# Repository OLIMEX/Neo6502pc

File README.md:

# Neo6502pc
World fastest 6502 computer. All in one Open Source Hardware and Software Modern Retro computer with real 6502 processor, HDMI, USB Flash drive, USB Gamepads, mouse, Keyboard support.

https://www.olimex.com/Products/Retro-Computers/Neo6502pc/open-source-hardware

## Licensee
* Hardware is released under CERN Open Hardware Licence Version 2 - Strongly Reciprocal
* Software is released under GPL V3 Licensee
* Documentation is released under CC BY-SA 4.0

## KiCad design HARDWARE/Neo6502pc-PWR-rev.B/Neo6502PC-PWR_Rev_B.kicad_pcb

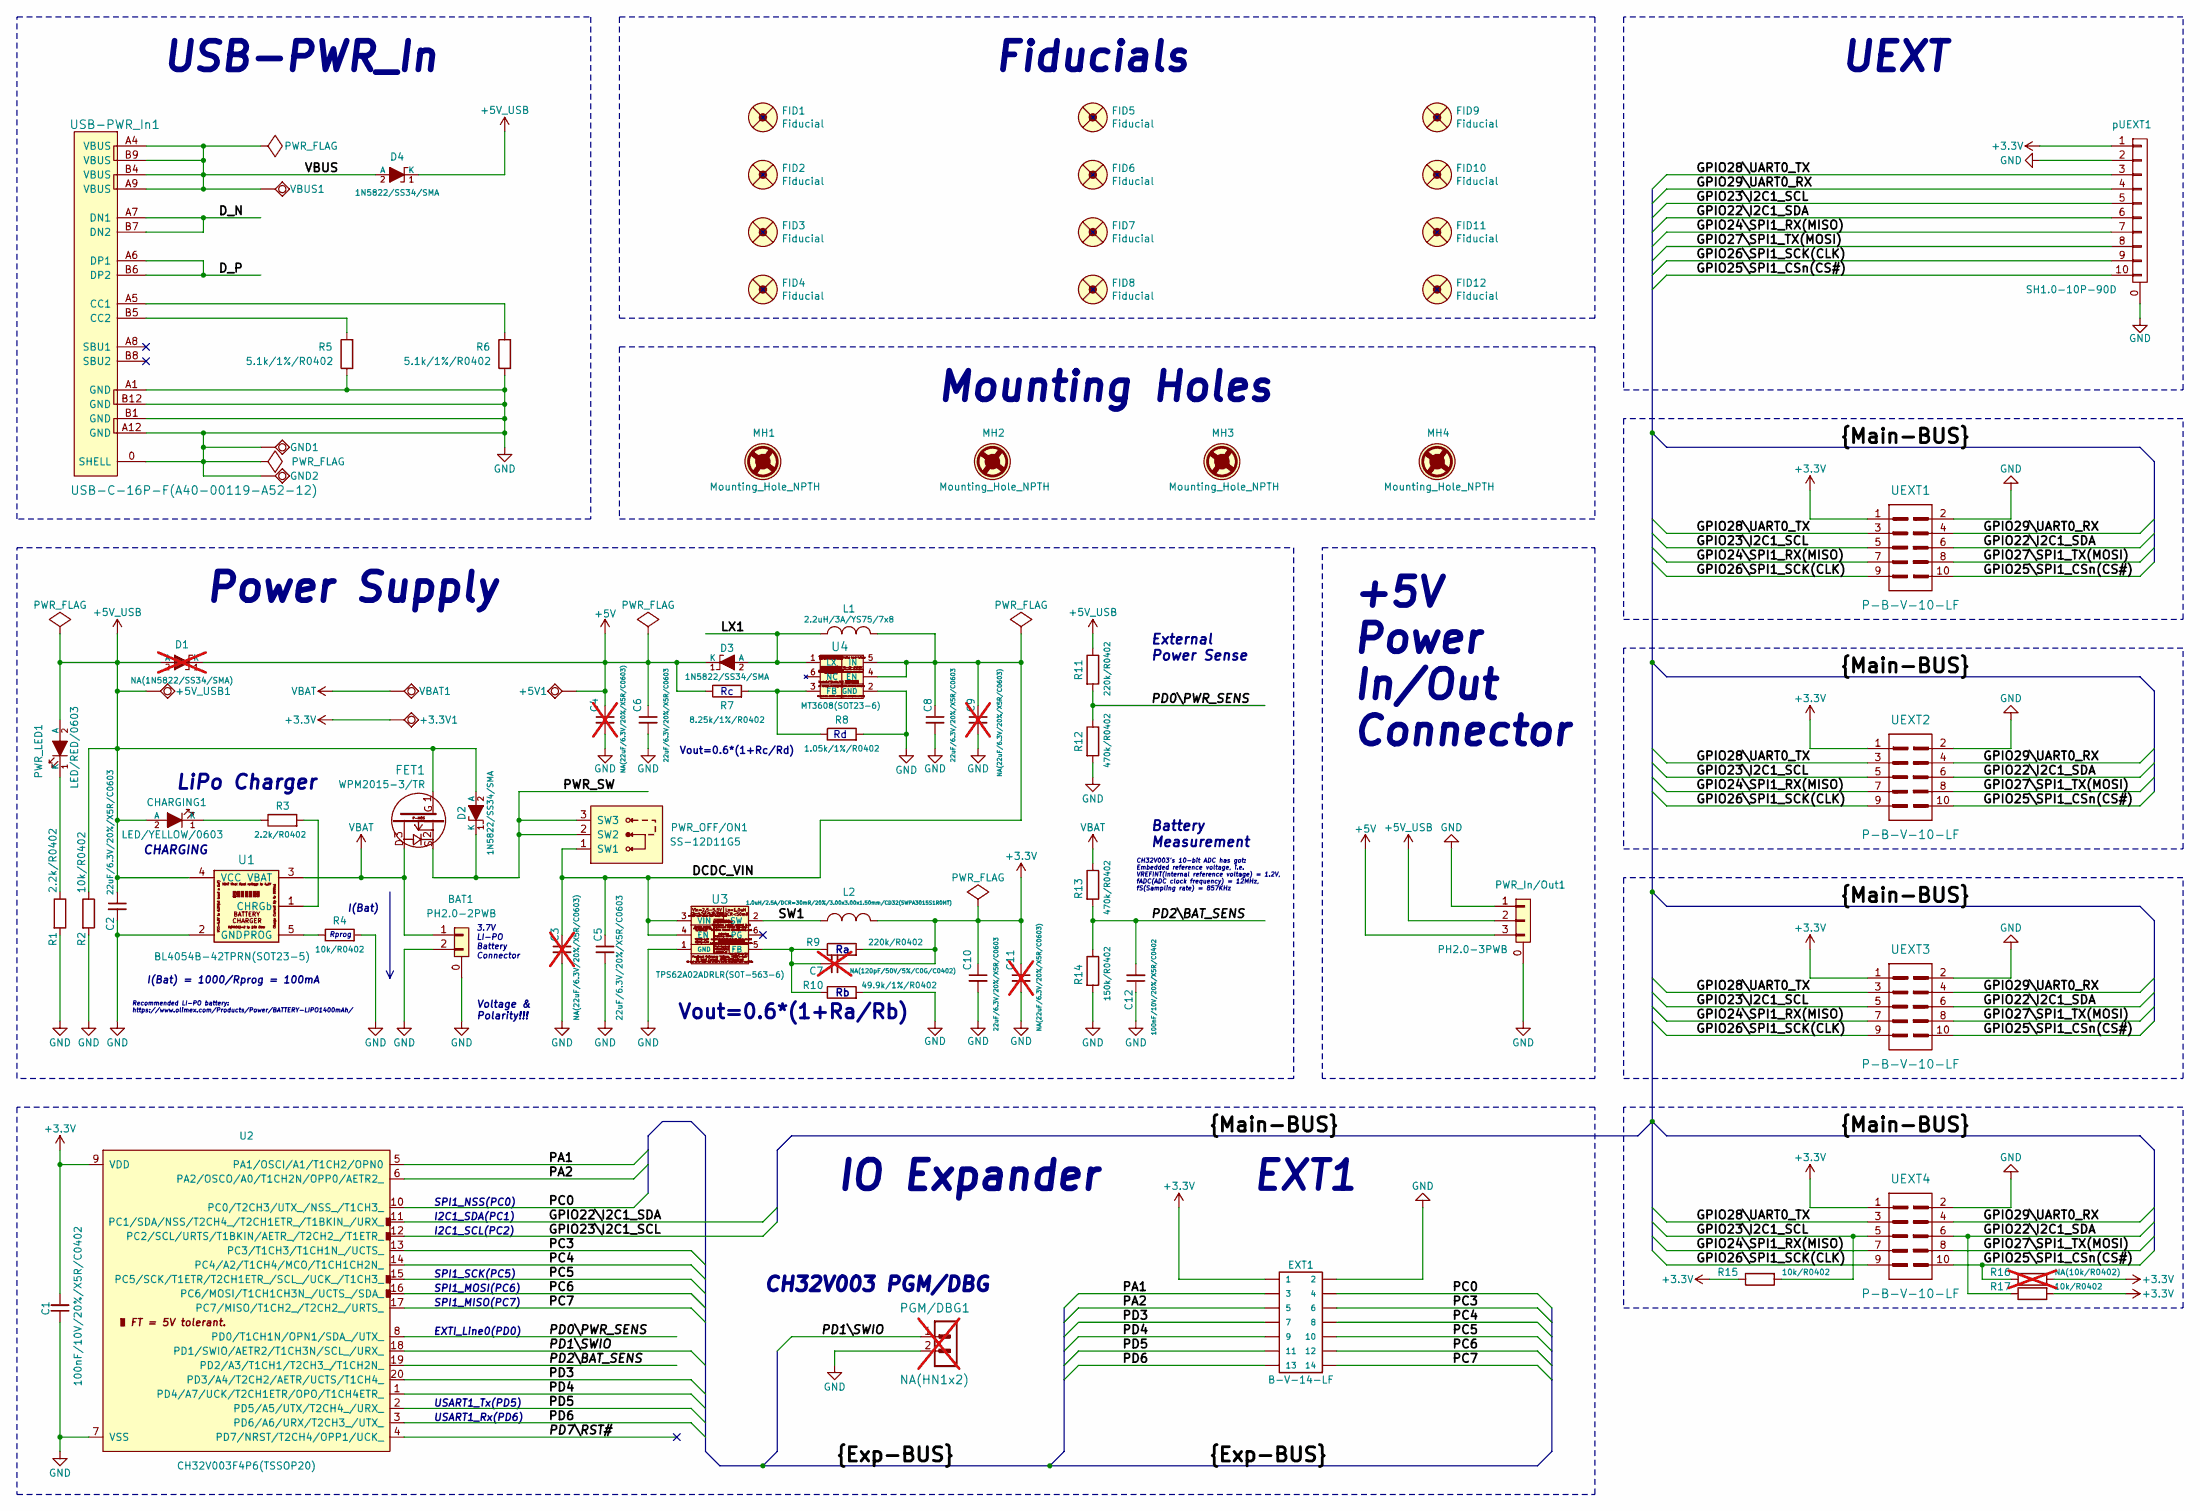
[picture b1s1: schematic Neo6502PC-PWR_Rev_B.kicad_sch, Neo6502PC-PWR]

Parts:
+3.3V1, +5V1, +5V_USB1: TESTPAD; TEST_PAD40x70_SQUARE
BAT1: PH2.0-2PWB
C1, C12: 100nF/10V/20%/X5R/C0402; C_0402_5MIL_DWS
C2, C5, C6, C8, C10: 22uF/6.3V/20%/X5R/C0603; C_0603_5MIL_DWS
C3, C4, C9, C11: NA(22uF/6.3V/20%/X5R/C0603); C_0603_5MIL_DWS; not fitted
C7: NA(120pF/50V/5%/C0G/C0402); C_0402_5MIL_DWS; not fitted
CHARGING1: LED/YELLOW/0603; LED_0603_KA
D1: NA(1N5822/SS34/SMA); SMA-KA; not fitted
D2, D3, D4: 1N5822/SS34/SMA; SMA-KA
EXT1: B-V-14-LF; GBH-254-SMT-14
FET1: WPM2015-3/TR; SOT23
FID1, FID2, FID3, FID4, FID5, FID7: Fiducial; Fiducial1x3_Paste
FID6, FID8, FID9, FID10, FID11, FID12: Fiducial; Fiducial1x3
GND1, GND2: TESTPAD; TEST_PAD40x70_SQUARE
L1: 2.2uH/3A/YS75/7x8; YS75_7X8MM
L2: 1.0uH/2.5A/DCR=30mR/20%/3.00x3.00x1.50mm/CD32(SWP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; CD32
MH1, MH2, MH3, MH4: Mounting_Hole_NPTH; Mounting_Hole_Drill-3.3mm_Clerance-7mm
PGM/DBG1: NA(HN1x2); HN1x2; not fitted
PWR_In/Out1: PH2.0-3PWB
PWR_LED1: LED/RED/0603; LED_0603_KA
PWR_OFF/ON1: SS-12D11G5
R1, R3: 2.2k/R0402; R_0402_5MIL_DWS
R2, R4, R15, R17: 10k/R0402; R_0402_5MIL_DWS
R5, R6: 5.1k/1%/R0402; R_0402_5MIL_DWS
R7: 8.25k/1%/R0402; R_0402_5MIL_DWS
R8: 1.05k/1%/R0402; R_0402_5MIL_DWS
R9, R11: 220k/R0402; R_0402_5MIL_DWS
R10: 49.9k/1%/R0402; R_0402_5MIL_DWS
R12, R13: 470k/R0402; R_0402_5MIL_DWS
R14: 150k/R0402; R_0402_5MIL_DWS
R16: NA(10k/R0402); R_0402_5MIL_DWS; not fitted
U1: BL4054B-42TPRN(SOT23-5); SOT-23-5
U2: CH32V003F4P6(TSSOP20); TSSOP20_Pitch-0.65mm_6.6x4.5x1.2mm
U3: TPS62A02ADRLR(SOT-563-6); SOT-563-6
U4: MT3608(SOT23-6); SOT23-6
UEXT1, UEXT2, UEXT3, UEXT4: P-B-V-10-LF; GBH-254-SMT-10
USB-PWR_In1: USB-C-16P-F(A40-00119-A52-12); USB2.0_TYPE-C(A40-00119-A52-12)_Paste
VBAT1: TESTPAD; TEST_PAD40x70_SQUARE
VBUS1: TESTPAD; TEST_PAD40x70_SQUARE
pUEXT1: SH1.0-10P-90D; SM10B-SRSS-TB

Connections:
+3.3V: +3.3V1.1 (Pad), C1.2, C7.2, C10.1, C11.1, EXT1.1, L2.2, R9.2, R15.1, R16.2, R17.2, U2.9 (VDD), UEXT1.1, UEXT2.1, UEXT3.1, UEXT4.1, pUEXT1.1
+5V: +5V1.1 (Pad), C4.1, C6.1, D1.1 (K), D3.1 (K), PWR_In/Out1.3 (P2), R7.1
+5V_USB: +5V_USB1.1 (Pad), C2.1, CHARGING1.2 (A), D1.2 (A), D2.2 (A), D4.1 (K), FET1.1, PWR_In/Out1.2, PWR_LED1.2 (A), R2.1, R11.1, U1.4 (VCC)
/DCDC_VIN: C3.1, C5.1, C8.1, C9.1, L1.2, PWR_OFF/ON1.1 (SW1), U3.3 (VIN), U3.4 (EN), U4.4 (EN), U4.5 (IN)
/D_N: USB-PWR_In1.A7 (DN1), USB-PWR_In1.B7 (DN2)
/D_P: USB-PWR_In1.A6 (DP1), USB-PWR_In1.B6 (DP2)
/GPIO22\I2C1_SDA: R17.1, U2.11 (PC1/SDA/NSS/T2CH4_/T2CH1ETR_/T1BKIN_/UR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), UEXT1.6, UEXT2.6, UEXT3.6, UEXT4.6, pUEXT1.6
/GPIO23\I2C1_SCL: R15.2, U2.12 (PC2/SCL/URTS/T1BKIN/AETR_/T2CH2_/T1ETR_), UEXT1.5, UEXT2.5, UEXT3.5, UEXT4.5, pUEXT1.5
/GPIO24\SPI1_RX(MISO): UEXT1.7, UEXT2.7, UEXT3.7, UEXT4.7, pUEXT1.7
/GPIO25\SPI1_CSn(CS#): R16.1, UEXT1.10, UEXT2.10, UEXT3.10, UEXT4.10, pUEXT1.10
/GPIO26\SPI1_SCK(CLK): UEXT1.9, UEXT2.9, UEXT3.9, UEXT4.9, pUEXT1.9
/GPIO27\SPI1_TX(MOSI): UEXT1.8, UEXT2.8, UEXT3.8, UEXT4.8, pUEXT1.8
/GPIO28\UART0_TX: UEXT1.3, UEXT2.3, UEXT3.3, UEXT4.3, pUEXT1.3
/GPIO29\UART0_RX: UEXT1.4, UEXT2.4, UEXT3.4, UEXT4.4, pUEXT1.4
/LX1: D3.2 (A), L1.1, U4.1 (LX)
/PA1: EXT1.3, U2.5 (PA1/OSCI/A1/T1CH2/OPN0)
/PA2: EXT1.5, U2.6 (PA2/OSCO/A0/T1CH2N/OPP0/AETR2_)
/PC0: EXT1.4, U2.10 (PC0/T2CH3/UTX_/NSS_/T1CH3_)
/PC3: EXT1.6, U2.13 (PC3/T1CH3/T1CH1N_/UCTS_)
/PC4: EXT1.8, U2.14 (PC4/A2/T1CH4/MCO/T1CH1CH2N_)
/PC5: EXT1.10, U2.15 (PC5/SCK/T1ETR/T2CH1ETR_/SCL_/UCK_/T1CH3_)
/PC6: EXT1.12, U2.16 (PC6/MOSI/T1CH1CH3N_/UCTS_/SDA_)
/PC7: EXT1.14, U2.17 (PC7/MISO/T1CH2_/T2CH2_/URTS_)
/PD0\PWR_SENS: R11.2, R12.1, U2.8 (PD0/T1CH1N/OPN1/SDA_/UTX_)
/PD1\SWIO: PGM/DBG1.1, U2.18 (PD1/SWIO/AETR2/T1CH3N/SCL_/URX_)
/PD2\BAT_SENS: C12.2, R13.2, R14.1, U2.19 (PD2/A3/T1CH1/T2CH3_/T1CH2N_)
/PD3: EXT1.7, U2.20 (PD3/A4/T2CH2/AETR/UCTS/T1CH4_)
/PD4: EXT1.9, U2.1 (PD4/A7/UCK/T2CH1ETR/OPO/T1CH4ETR_)
/PD5: EXT1.11, U2.2 (PD5/A5/UTX/T2CH4_/URX_)
/PD6: EXT1.13, U2.3 (PD6/A6/URX/T2CH3_/UTX_)
/PD7\RST#: U2.4 (PD7/NRST/T2CH4/OPP1/UCK_)
/PWR_SW: D2.1 (K), FET1.2, PWR_OFF/ON1.2 (SW2), PWR_OFF/ON1.3 (SW3)
/SW1: L2.1, U3.2 (SW)
/VBUS: D4.2 (A), USB-PWR_In1.A4 (VBUS), USB-PWR_In1.A9 (VBUS), USB-PWR_In1.B4 (VBUS), USB-PWR_In1.B9 (VBUS), VBUS1.1 (Pad)
GND: BAT1.0, BAT1.2, C1.1, C2.2, C3.2, C4.2, C5.2, C6.2, C8.2, C9.2, C10.2, C11.2, C12.1, EXT1.2, GND1.1 (Pad), GND2.1 (Pad), PGM/DBG1.2, PWR_In/Out1.0, PWR_In/Out1.1, R1.2, R2.2, R4.2, R5.1, R6.1, R8.2, R10.2, R12.2, R14.2, U1.2 (GND), U2.7 (VSS), U3.1 (GND), U4.2 (GND), UEXT1.2, UEXT2.2, UEXT3.2, UEXT4.2, USB-PWR_In1.0 (SHELL), USB-PWR_In1.A1 (GND), USB-PWR_In1.A12 (GND), USB-PWR_In1.B1 (GND), USB-PWR_In1.B12 (GND), pUEXT1.0, pUEXT1.2
unnamed: CHARGING1.1 (K), R3.1
unnamed: PWR_LED1.1 (K), R1.1
unnamed: R3.2, U1.1 (CHRGb)
unnamed: R4.1, U1.5 (PROG)
unnamed: C7.1, R9.1, R10.1, U3.5 (FB)
unnamed: R7.2, R8.1, U4.3 (FB)
unnamed: R6.2, USB-PWR_In1.A5 (CC1)
unnamed: R5.2, USB-PWR_In1.B5 (CC2)
VBAT: BAT1.1, FET1.3, R13.1, U1.3 (VBAT), VBAT1.1 (Pad)

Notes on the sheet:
I(Bat) = 1000/Rprog = 100mA
CHARGING
CH32V003 PGM/DBG
SPI1_MOSI(PC6)
Rprog
External Power Sense
I2C1_SCL(PC2)
SPI1_MISO(PC7)
Fiducials
EXT1
Recommended LI-PO battery: https://www.olimex.com/Products/Power/BATTERY-LIPO1400mAh/
LiPo Charger
Power Supply
I(Bat)
Mounting Holes
EXTI_Line0(PD0)
I2C1_SDA(PC1)
USART1_Rx(PD6)
Vout=0.6*(1+Rc/Rd)
Vout=0.6*(1+Ra/Rb)
SPI1_NSS(PC0)
USART1_Tx(PD5)
3.7V LI-PO Battery Connector
CH32V003's 10-bit ADC has got: Embedded reference voltage, i.e. VREFINT(Internal reference voltage) = 1.2V, fADC(ADC clock frequency) = 12MHz, fS(Sampling rate) = 857KHz
UEXT
IO Expander
+5V Power In/Out Connector
SPI1_SCK(PC5)
USB-PWR_In
Voltage & Polarity!!!
Battery Measurement

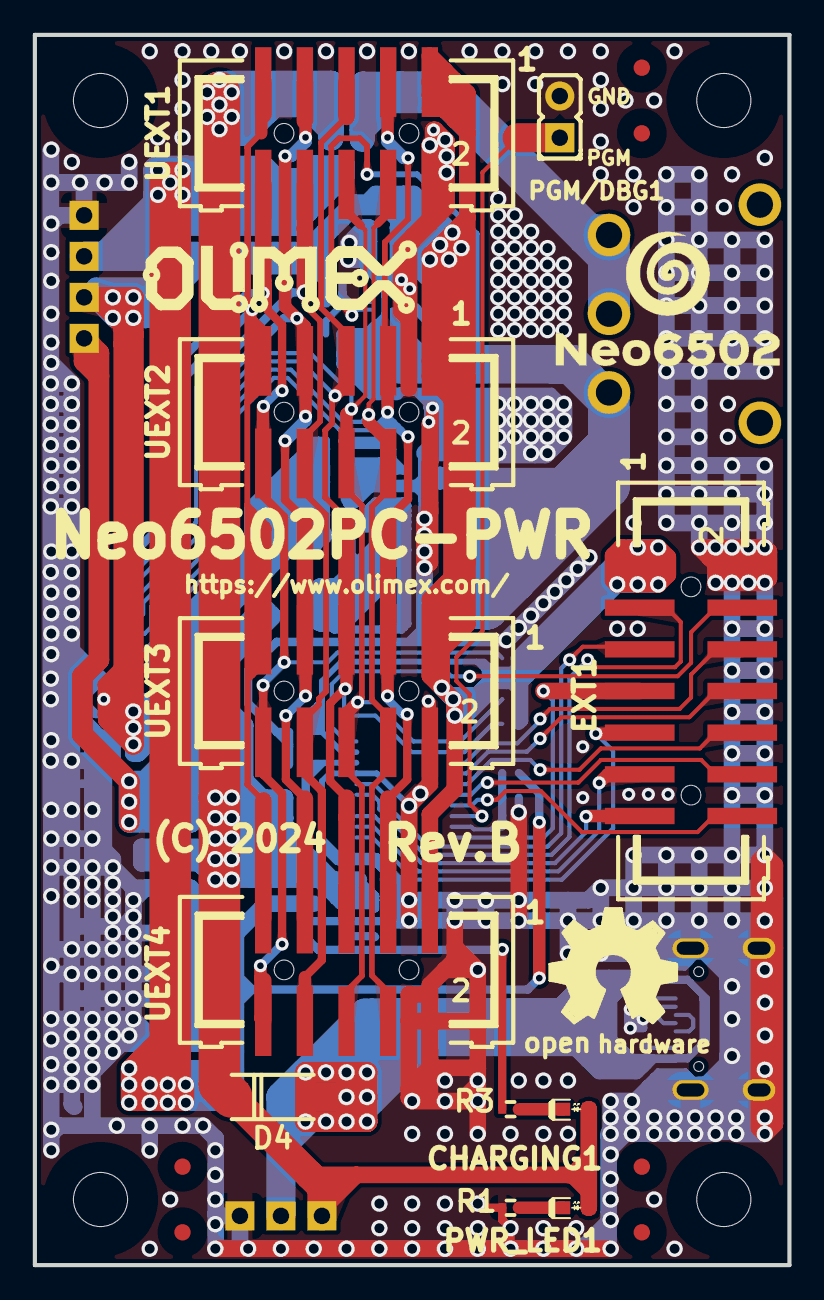
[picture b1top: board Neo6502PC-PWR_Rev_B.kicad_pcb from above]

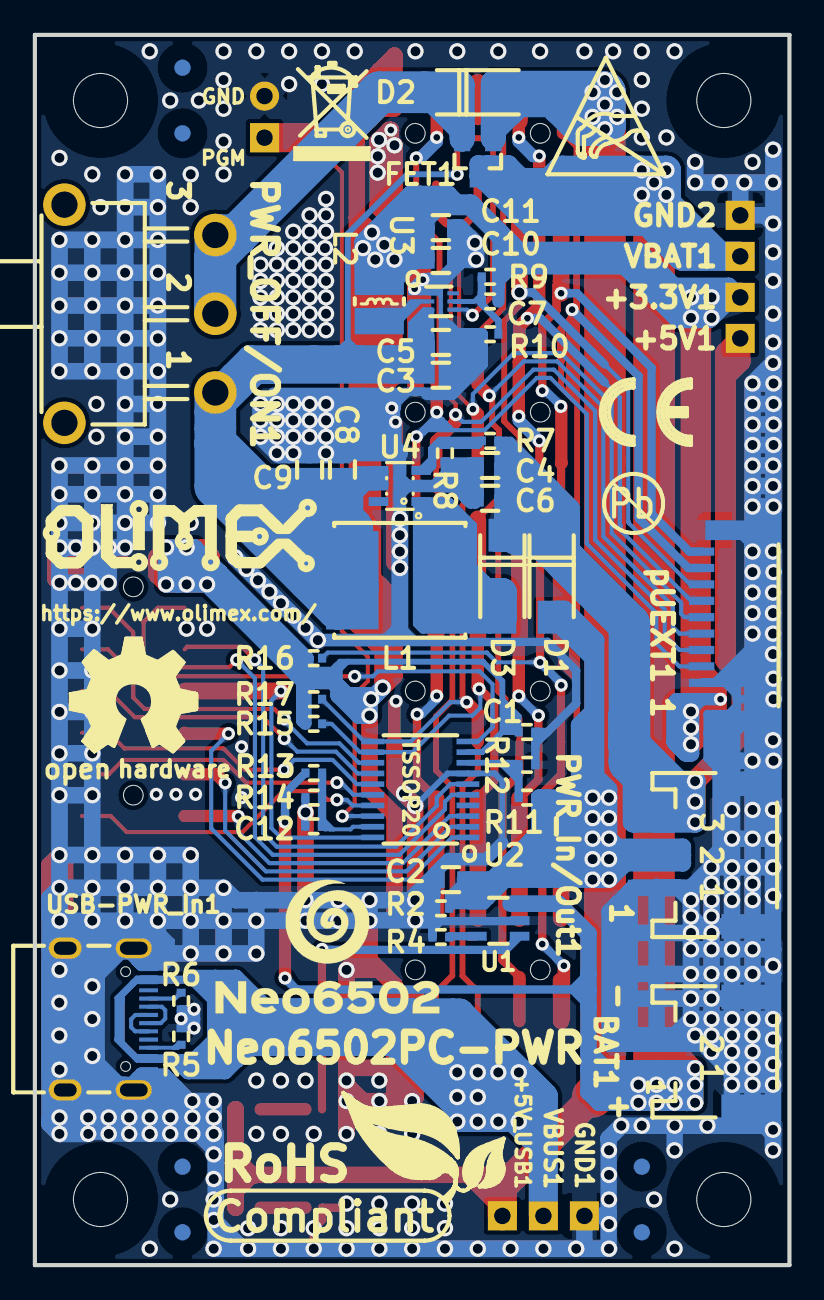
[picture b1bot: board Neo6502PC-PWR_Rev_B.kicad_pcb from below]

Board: 2 copper layers, 46.0 x 75.0 mm, 87 parts (63 on the bottom side), 43 nets.

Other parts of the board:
Logo_OLIMEX_TB-Bottom: Logo_OLIMEX_TB
Logo_OLIMEX_TB-Top: Logo_OLIMEX_TB
NEO_LOGO_SMALL*: LOGO; Neo6502_Sign_Small
NEO_LOGO_SMALL_Top*: LOGO; Neo6502_Sign_Small
Sign_Antistatic: Sign_Antistatic
Sign_CE: CE_Sign
Sign_OSHW_8x8, Sign_OSHW_8x8-Top: Sign_OSHW_8x8
Sign_PB-Free: Sign_PB-Free
Sign_RecycleBin: Sign_RecycleBin; Sign_RecycleBin_1
Sign_RoHS: Sign_RoHS; Sign_RoHS_1

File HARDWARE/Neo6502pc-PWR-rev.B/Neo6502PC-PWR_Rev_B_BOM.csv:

Quantity,Value,Footprint,Reference
1,PH2.0-2PWB,PH2.0-2PWB,BAT1
2,100nF/10V/20%/X5R/C0402,C_0402_5MIL_DWS,"C1, C12"
5,22uF/6.3V/20%/X5R/C0603,C_0603_5MIL_DWS,"C2, C5, C6, C8, C10"
1,LED/YELLOW/0603,LED_0603_KA,CHARGING1
3,1N5822/SS34/SMA,SMA-KA,"D2, D3, D4"
1,B-V-14-LF,GBH-254-SMT-14,EXT1
1,WPM2015-3/TR,SOT23,FET1
1,2.2uH/3A/YS75/7x8,YS75_7X8MM,L1
1,1.0uH/2.5A/DCR=30mR/20%/3.00x3.00x1.50mm/CD32(SWPA3015S1R0MT),CD32,L2
1,PH2.0-3PWB,PH2.0-3PWB,PWR_In/Out1
1,LED/RED/0603,LED_0603_KA,PWR_LED1
1,SS-12D11G5,SS-12D11G5,PWR_OFF/ON1
2,2.2k/R0402,R_0402_5MIL_DWS,"R1, R3"
4,10k/R0402,R_0402_5MIL_DWS,"R2, R4, R15, R17"
2,5.1k/1%/R0402,R_0402_5MIL_DWS,"R5, R6"
1,8.25k/1%/R0402,R_0402_5MIL_DWS,R7
1,1.05k/1%/R0402,R_0402_5MIL_DWS,R8
2,220k/R0402,R_0402_5MIL_DWS,"R9, R11"
1,49.9k/1%/R0402,R_0402_5MIL_DWS,R10
2,470k/R0402,R_0402_5MIL_DWS,"R12, R13"
1,150k/R0402,R_0402_5MIL_DWS,R14
1,BL4054B-42TPRN(SOT23-5),SOT-23-5,U1
1,CH32V003F4P6(TSSOP20),TSSOP20_Pitch-0.65mm_6.6x4.5x1.2mm,U2
1,TPS62A02ADRLR(SOT-563-6),SOT-563-6,U3
1,MT3608(SOT23-6),SOT23-6,U4
4,P-B-V-10-LF,GBH-254-SMT-10,"UEXT1, UEXT2, UEXT3, UEXT4"
1,USB-C-16P-F(A40-00119-A52-12),USB2.0_TYPE-C(A40-00119-A52-12)_Paste,USB-PWR_In1
1,SH1.0-10P-90D,SM10B-SRSS-TB,pUEXT1

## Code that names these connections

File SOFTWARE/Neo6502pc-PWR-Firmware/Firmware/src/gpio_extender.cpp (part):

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	{},                     //
	{},                     // +3.3V #1
	{},                     // GND   #2
	{GPIOA, GPIO_Pin_1},    // PA1   #3
	{GPIOC, GPIO_Pin_0},    // PC0   #4
	{GPIOA, GPIO_Pin_2},    // PA2   #5
	{GPIOC, GPIO_Pin_3},    // PC3   #6
	{GPIOD, GPIO_Pin_3},    // PD3   #7
	{GPIOC, GPIO_Pin_4},    // PC4   #8
	{GPIOD, GPIO_Pin_4},    // PD4   #9
	{GPIOC, GPIO_Pin_5},    // PC5   #10
	{GPIOD, GPIO_Pin_5},    // PD5   #11
	{GPIOC, GPIO_Pin_6},    // PC6   #12
	{GPIOD, GPIO_Pin_6},    // PD6   #13
	{GPIOC, GPIO_Pin_7},    // PC7   #14
	{GPIOD, GPIO_Pin_0},    // PD0   #15 PWR_SENS
};

// Initial GPIO extender cofiguration
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
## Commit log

2024-06-25 initial upload
2024-06-25 add copyright message to the sources
2024-06-27 update firmware
2024-07-09 FIX: BAT_SENS percent calibration
    Changed EXT_GPIO_BATSENS_MIN and EXT_GPIO_BATSENS_MAX values
2024-07-09 Improved ADC measurement
    Added possibility to average several consecutive measurements for better precision
2024-07-09 Firmware version changed to 1.1
2024-07-10 update user manual
2024-12-16 Update
    Manual

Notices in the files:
HARDWARE/Neo6502pc-PWR-rev.B/Neo6502PC-PWR_Rev_B.kicad_pcb:
(C) 2024
